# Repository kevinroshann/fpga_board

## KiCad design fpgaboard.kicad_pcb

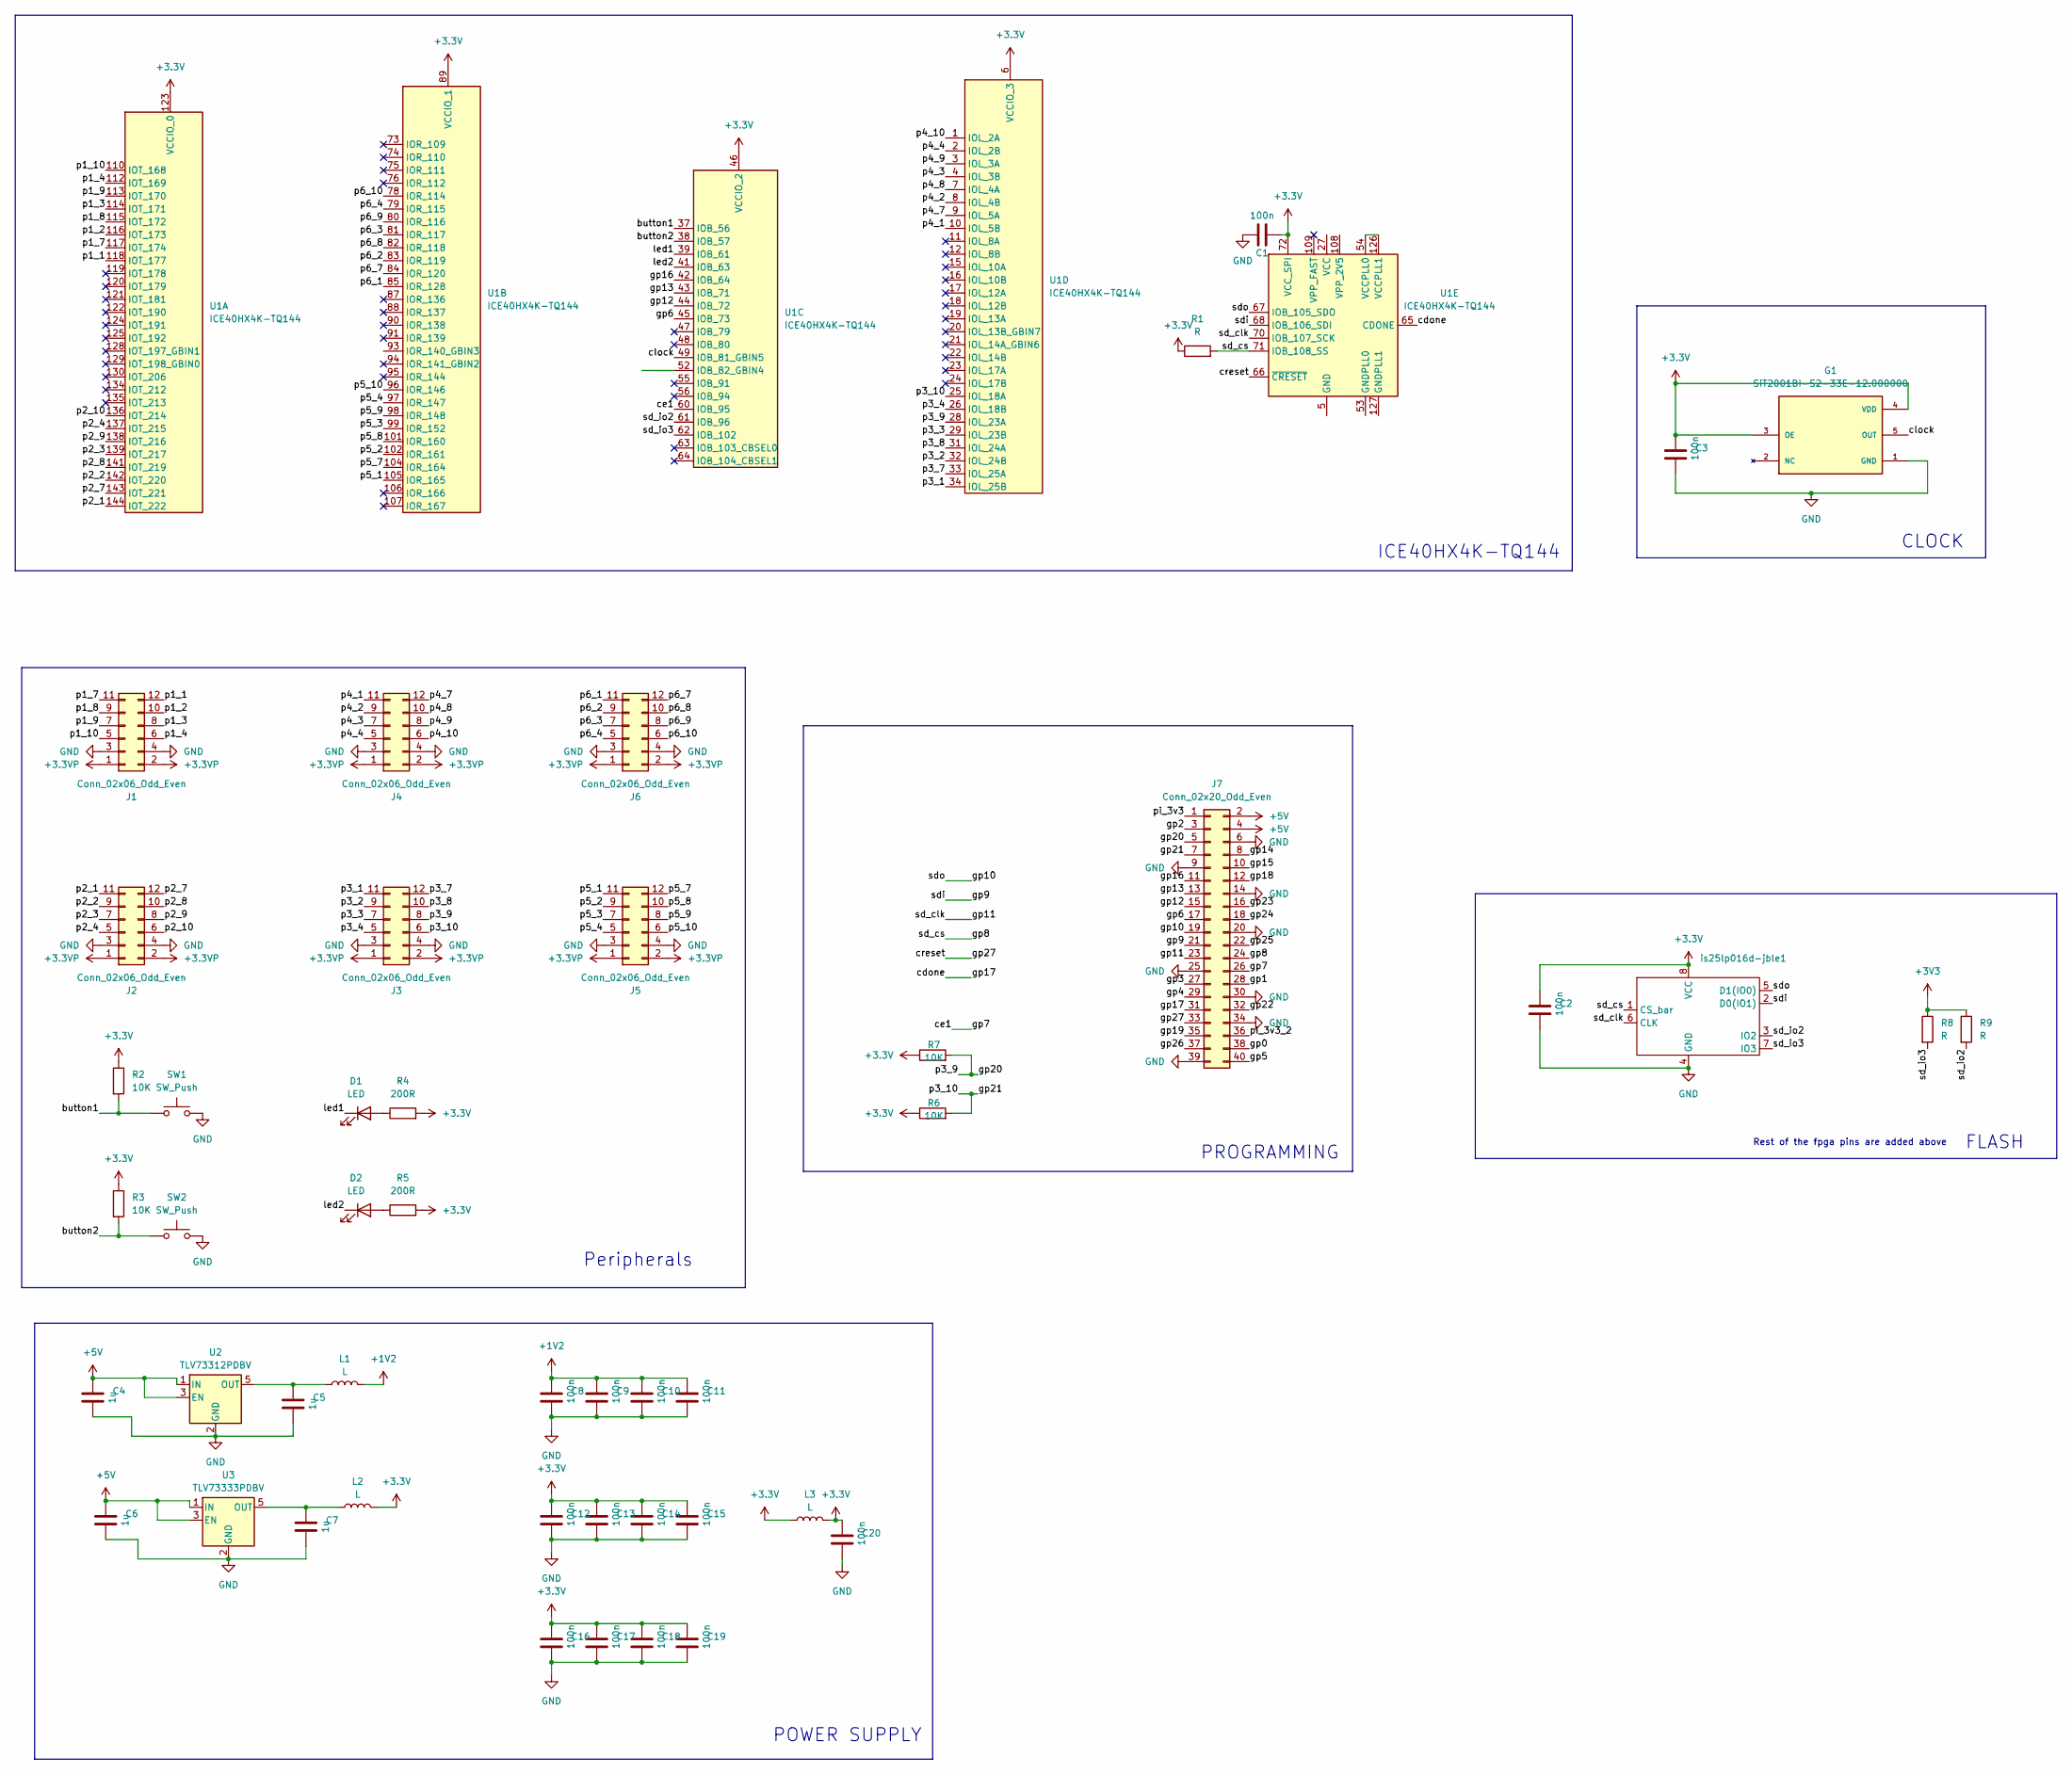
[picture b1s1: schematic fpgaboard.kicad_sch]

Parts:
C1, C2, C3, C8, C9, C10, C11, C12, C13, C14, C15, C16, C17, C18, C19, C20: 100n; C_0201_0603Metric_Pad0.64x0.40mm_HandSolder
C4, C5, C6, C7: 1u; C_0201_0603Metric_Pad0.64x0.40mm_HandSolder
D1, D2: LED; LED_0201_0603Metric_Pad0.64x0.40mm_HandSolder
G1: SiT2001BI-S2-33E-12.000000; SOT95P280X145-5N; PARTREV 1.03
J1, J2, J3, J4, J5, J6: Conn_02x06_Odd_Even; PinSocket_2x06_P2.54mm_Horizontal
J7: Conn_02x20_Odd_Even; PinSocket_2x20_P2.54mm_Horizontal
L1, L2, L3: L; L_0201_0603Metric_Pad0.64x0.40mm_HandSolder
R1, R8, R9: R; R_0201_0603Metric_Pad0.64x0.40mm_HandSolder
R2, R3, R6, R7: 10K; R_0201_0603Metric_Pad0.64x0.40mm_HandSolder
R4, R5: 200R; R_0201_0603Metric_Pad0.64x0.40mm_HandSolder
SW1, SW2: SW_Push; SW_DIP_SPSTx01_Slide_6.7x4.1mm_W7.62mm_P2.54mm_LowProfile
U1: ICE40HX4K-TQ144; TQFP-144_20x20mm_P0.5mm
U2: TLV73312PDBV; SOT-23-5
U3: TLV73333PDBV; SOT-23-5
is25lp016d-jble1: SOIC127P790X216-8N

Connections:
+1V2: C8.1, C9.1, C10.1, C11.1, L1.2
+3.3V: C1.2, C2.1, C3.1, C12.1, C13.1, C14.1, C15.1, C16.1, C17.1, C18.1, C19.1, C20.1, G1.3 (OE), G1.4 (VDD), L2.2, L3.1, L3.2, R1.1, R2.1, R3.1, R4.2, R5.2, R6.1, R7.1, U1.6 (VCCIO_3), U1.30 (VCCIO_3), U1.46 (VCCIO_2), U1.57 (VCCIO_2), U1.72 (VCC_SPI), U1.89 (VCCIO_1), U1.100 (VCCIO_1), U1.123 (VCCIO_0), U1.131 (VCCIO_0), is25lp016d-jble1.8 (VCC)
+3.3VP: J1.1, J1.2, J2.1, J2.2, J3.1, J3.2, J4.1, J4.2, J5.1, J5.2, J6.1, J6.2
+3V3: R8.1, R9.1
+5V: C4.1, C6.1, J7.2, J7.4, U2.1 (IN), U2.3 (EN), U3.1 (IN), U3.3 (EN)
/button1: R2.2, SW1.1, U1.37 (IOB_56)
/button2: R3.2, SW2.1, U1.38 (IOB_57)
/cdone: J7.31, U1.65 (CDONE)
/ce1: J7.26, U1.60 (IOB_95)
/clock: G1.5 (OUT), U1.49 (IOB_81_GBIN5)
/creset: J7.33, U1.66 (~CRESET)
/gp0: J7.38
/gp1: J7.28
/gp2: J7.3
/gp3: J7.27
/gp4: J7.29
/gp5: J7.40
/gp6: J7.17, U1.45 (IOB_73)
/gp8: J7.24, R1.2, U1.71 (IOB_108_SS), is25lp016d-jble1.1 (CS_bar)
/gp9: J7.21, U1.68 (IOB_106_SDI), is25lp016d-jble1.2 (D0(IO1))
/gp10: J7.19, U1.67 (IOB_105_SDO), is25lp016d-jble1.5 (D1(IO0))
/gp11: J7.23, U1.70 (IOB_107_SCK), is25lp016d-jble1.6 (CLK)
/gp12: J7.15, U1.44 (IOB_72)
/gp13: J7.13, U1.43 (IOB_71)
/gp14: J7.8
/gp15: J7.10
/gp16: J7.11, U1.42 (IOB_64)
/gp18: J7.12
/gp19: J7.35
/gp20: J3.8, J7.5, R7.2, U1.28 (IOL_23A)
/gp21: J3.6, J7.7, R6.2, U1.25 (IOL_18A)
/gp22: J7.32
/gp23: J7.16
/gp24: J7.18
/gp25: J7.22
/gp26: J7.37
/led1: D1.1 (K), U1.39 (IOB_61)
/led2: D2.1 (K), U1.41 (IOB_63)
/p1_1: J1.12, U1.118 (IOT_177)
/p1_2: J1.10, U1.116 (IOT_173)
/p1_3: J1.8, U1.114 (IOT_171)
/p1_4: J1.6, U1.112 (IOT_169)
/p1_7: J1.11, U1.117 (IOT_174)
/p1_8: J1.9, U1.115 (IOT_172)
/p1_9: J1.7, U1.113 (IOT_170)
/p1_10: J1.5, U1.110 (IOT_168)
/p2_1: J2.11, U1.144 (IOT_222)
/p2_2: J2.9, U1.142 (IOT_220)
/p2_3: J2.7, U1.139 (IOT_217)
/p2_4: J2.5, U1.137 (IOT_215)
/p2_7: J2.12, U1.143 (IOT_221)
/p2_8: J2.10, U1.141 (IOT_219)
/p2_9: J2.8, U1.138 (IOT_216)
/p2_10: J2.6, U1.136 (IOT_214)
/p3_1: J3.11, U1.34 (IOL_25B)
/p3_2: J3.9, U1.32 (IOL_24B)
/p3_3: J3.7, U1.29 (IOL_23B)
/p3_4: J3.5, U1.26 (IOL_18B)
/p3_7: J3.12, U1.33 (IOL_25A)
/p3_8: J3.10, U1.31 (IOL_24A)
/p4_1: J4.11, U1.10 (IOL_5B)
/p4_2: J4.9, U1.8 (IOL_4B)
/p4_3: J4.7, U1.4 (IOL_3B)
/p4_4: J4.5, U1.2 (IOL_2B)
/p4_7: J4.12, U1.9 (IOL_5A)
/p4_8: J4.10, U1.7 (IOL_4A)
/p4_9: J4.8, U1.3 (IOL_3A)
/p4_10: J4.6, U1.1 (IOL_2A)
/p5_1: J5.11, U1.105 (IOR_165)
/p5_2: J5.9, U1.102 (IOR_161)
/p5_3: J5.7, U1.99 (IOR_152)
/p5_4: J5.5, U1.97 (IOR_147)
/p5_7: J5.12, U1.104 (IOR_164)
/p5_8: J5.10, U1.101 (IOR_160)
/p5_9: J5.8, U1.98 (IOR_148)
/p5_10: J5.6, U1.96 (IOR_146)
/p6_1: J6.11, U1.85 (IOR_128)
/p6_2: J6.9, U1.83 (IOR_119)
/p6_3: J6.7, U1.81 (IOR_117)
/p6_4: J6.5, U1.79 (IOR_115)
/p6_7: J6.12, U1.84 (IOR_120)
/p6_8: J6.10, U1.82 (IOR_118)
/p6_9: J6.8, U1.80 (IOR_116)
/p6_10: J6.6, U1.78 (IOR_114)
/pi_3v3: J7.1
/pi_3v3_2: J7.36
/sd_io2: R9.2, U1.61 (IOB_96), is25lp016d-jble1.3 (IO2)
/sd_io3: R8.2, U1.62 (IOB_102), is25lp016d-jble1.7 (IO3)
GND: C1.1, C2.2, C3.2, C4.2, C5.2, C6.2, C7.2, C8.2, C9.2, C10.2, C11.2, C12.2, C13.2, C14.2, C15.2, C16.2, C17.2, C18.2, C19.2, C20.2, G1.1 (GND), J1.3, J1.4, J2.3, J2.4, J3.3, J3.4, J4.3, J4.4, J5.3, J5.4, J6.3, J6.4, J7.6, J7.9, J7.14, J7.20, J7.25, J7.30, J7.34, J7.39, SW1.2, SW2.2, U2.2 (GND), U3.2 (GND), is25lp016d-jble1.4 (GND)
unnamed: D1.2 (A), R4.1
unnamed: D2.2 (A), R5.1
unnamed: U1.5 (GND), U1.13 (GND), U1.14 (GND), U1.59 (GND), U1.69 (GND), U1.86 (GND), U1.103 (GND), U1.132 (GND), U1.140 (GND)
unnamed: U1.27 (VCC), U1.40 (VCC), U1.92 (VCC), U1.111 (VCC)
unnamed: U1.54 (VCCPLL0), U1.126 (VCCPLL1)
unnamed: C5.1, L1.1, U2.5 (OUT)
unnamed: C7.1, L2.1, U3.5 (OUT)

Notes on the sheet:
Peripherals
Rest of the fpga pins are added above
FLASH
CLOCK
POWER SUPPLY
PROGRAMMING
ICE40HX4K-TQ144

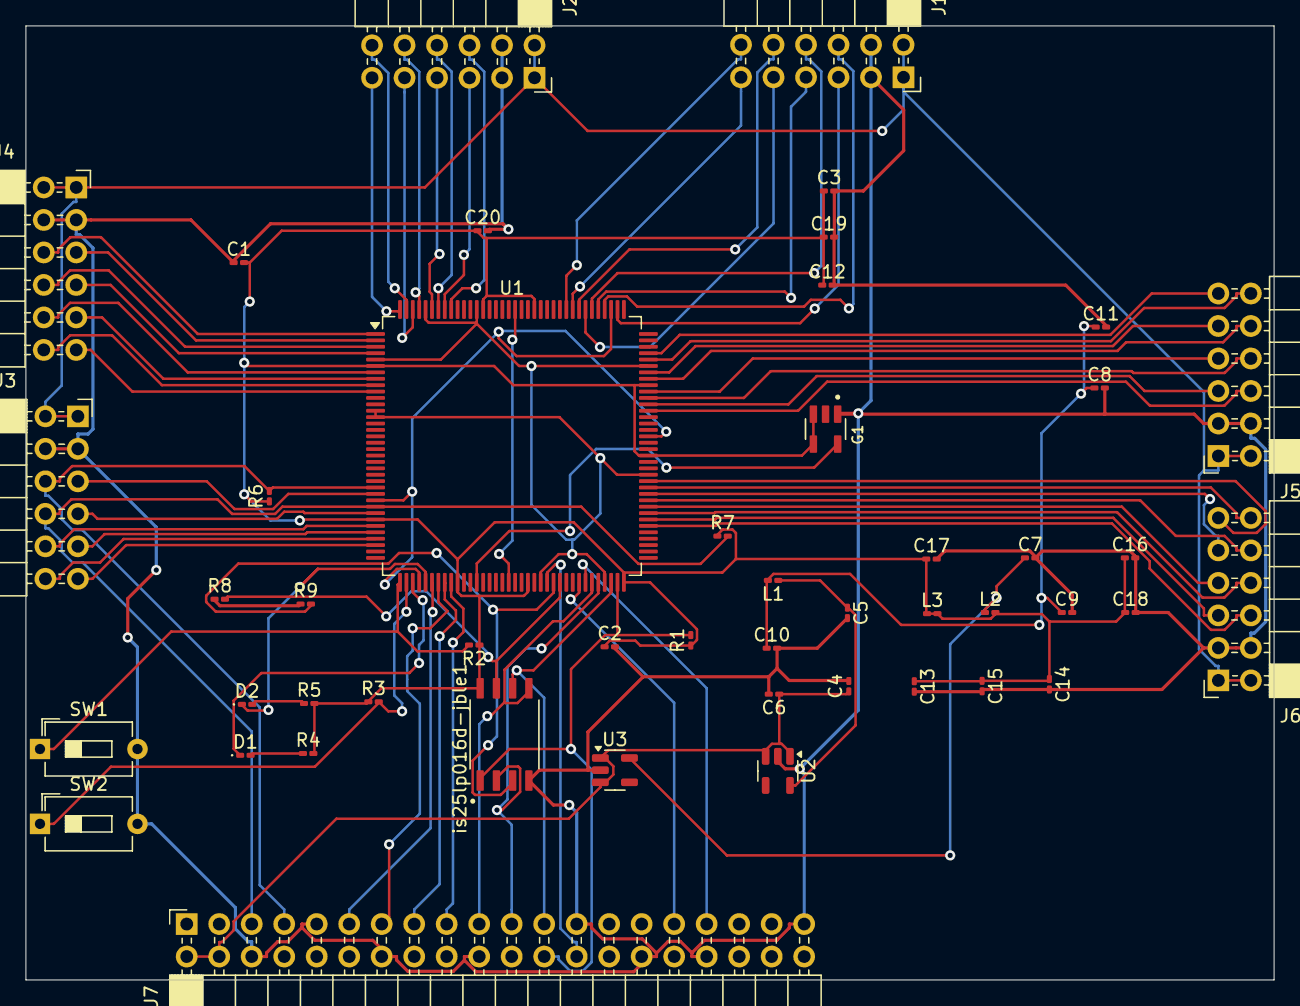
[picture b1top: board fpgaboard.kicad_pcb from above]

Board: 2 copper layers, 97.6 x 74.6 mm, 48 parts (0 on the bottom side), 79 nets.

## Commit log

2026-03-07 flash added
2026-03-07 test
2026-03-07 fpgaboard
